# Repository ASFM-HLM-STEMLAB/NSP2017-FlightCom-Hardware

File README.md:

# NSP2017-FlightCom-Hardware 
ASFM Near Space Program 2017 - Flight Computer Hardware for HLM1 Capsule

- Designed in Autodesk Eagle.
- Uses Particle Electron as the master Micro Controller Unit

## Files
* HLM1_CNC : 
	This files are for creating a prototype board using a CNC such as shapeoko.
* HLM1_Oursourced : 
	This files are for sending the board to a fab house to be made such as OshPark

## PCB Manufacturing
* You may order a PCB from our [OSHPARK PROJECT R1.0](https://www.oshpark.com/projects/XPm0Xe82)
* You may order a PCB from our [OSHPARK PROJECT R2.1](https://www.adafruit.com/product/3686)
* NOTE: R2.1 includes XBee Radio. GPS IO changed to software serial.

##### Designed and created at ASFM Monterrey Mexico, 2017-2018 @ Humberto Lobo Morales STEM LAB

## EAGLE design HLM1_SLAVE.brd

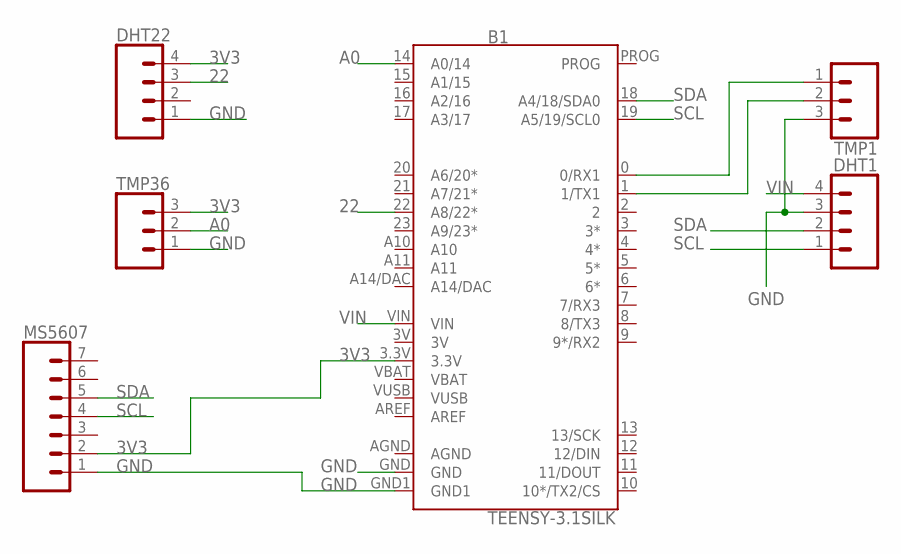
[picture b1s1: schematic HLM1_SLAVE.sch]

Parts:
B1: TEENSY-3.1SILK; TEENSY-3.1
DHT1, DHT22: CONN_04; 1X04
MS5607: CONN_07; 1X07
TMP1, TMP36: CONN_03; 1X03

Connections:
3V: B1.3V
3V3: B1.3.3V, DHT22.4, MS5607.2, TMP36.3
22: B1.22 (A8/22*), DHT22.3
A0: B1.14 (A0/14), TMP36.2
AGND: B1.AGND
GND: B1.GND, B1.GND1, DHT1.3, DHT22.1, MS5607.1, TMP1.3, TMP36.1
unnamed: B1.0 (0/RX1), TMP1.1
unnamed: B1.1 (1/TX1), TMP1.2
SCL: B1.19 (A5/19/SCL0), DHT1.1, MS5607.4
SDA: B1.18 (A4/18/SDA0), DHT1.2, MS5607.5
VBAT: B1.VBAT
VIN: B1.VIN, DHT1.4
VUSB: B1.VUSB

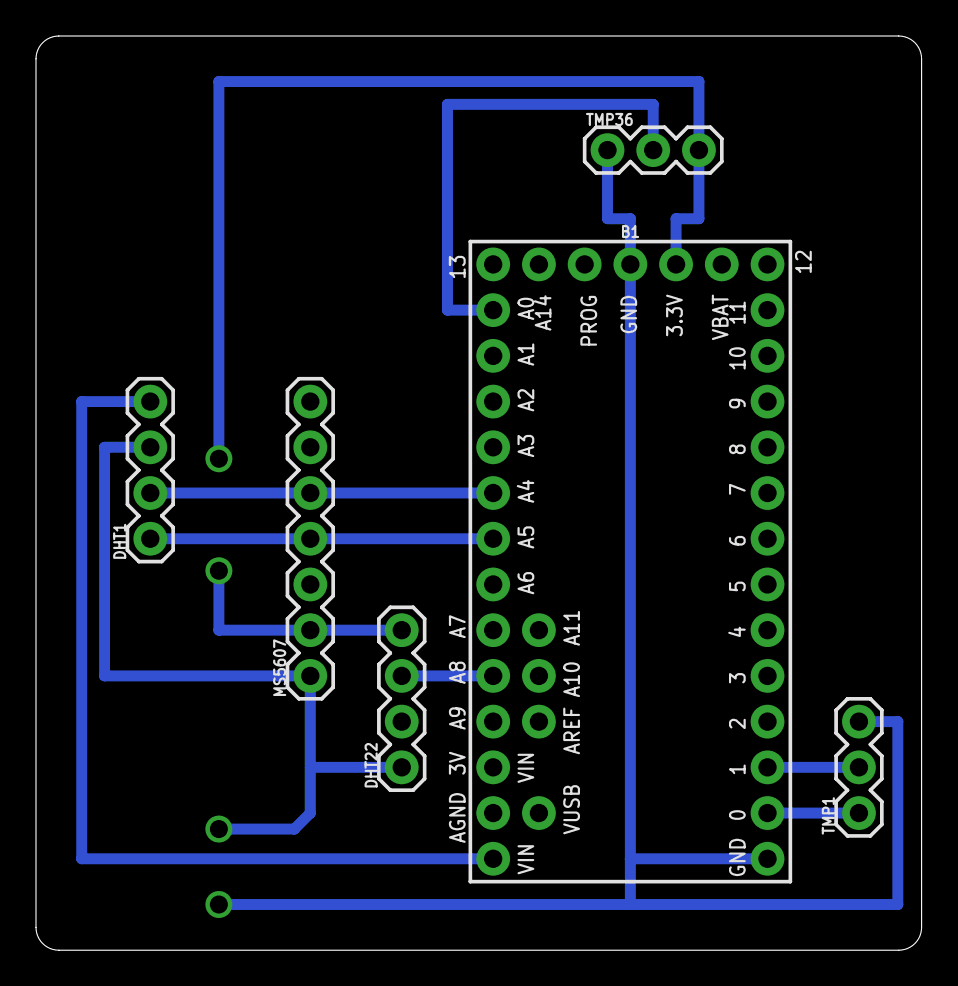
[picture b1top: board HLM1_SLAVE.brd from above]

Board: 2 copper layers, 49.2 x 50.8 mm, 6 parts (0 on the bottom side), 9 nets.

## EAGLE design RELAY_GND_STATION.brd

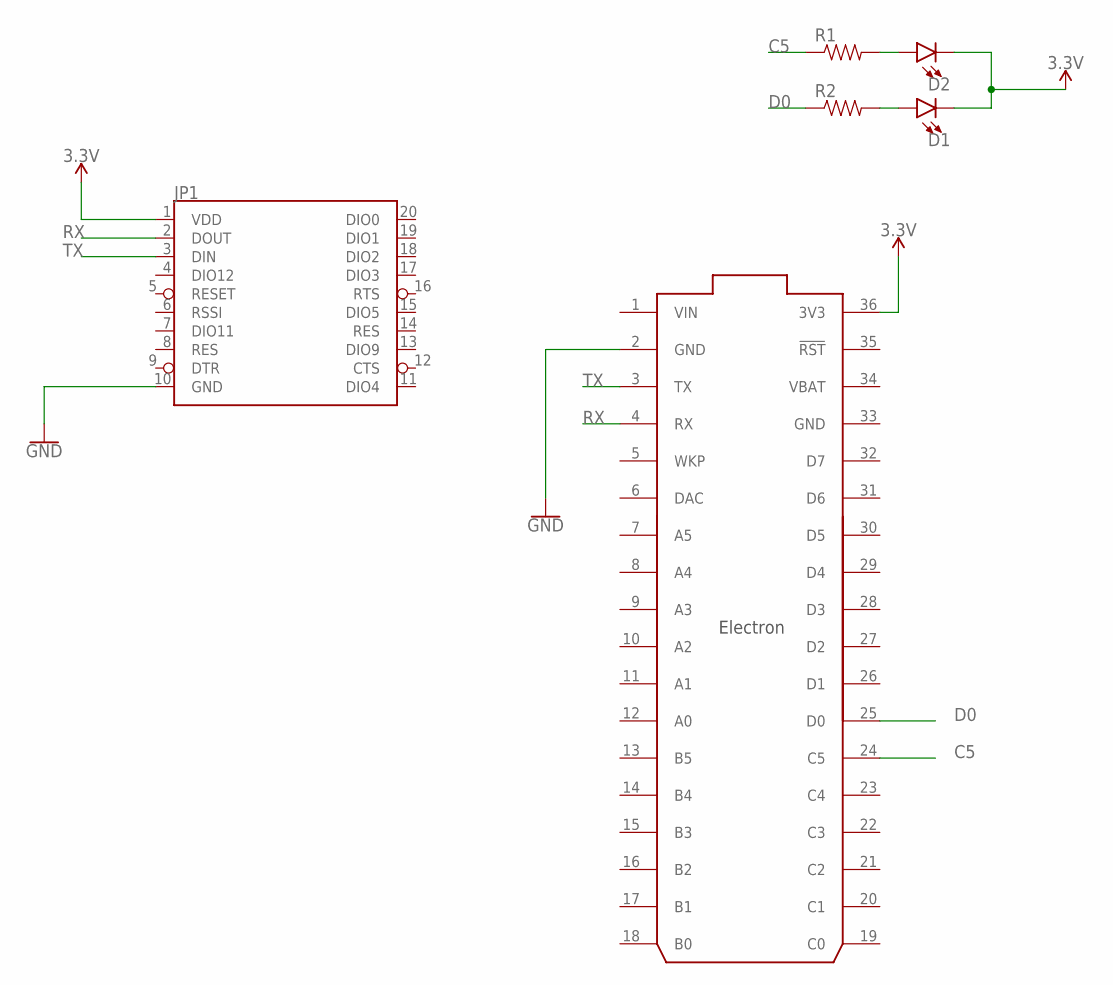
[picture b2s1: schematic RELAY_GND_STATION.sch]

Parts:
D1, D2: LED-3MM-NO_SILK; LED_3MM-NS
JP1: XBEELONGPAD; XBEE-LONGPAD
R1, R2: RESISTORKIT; AXIAL-0.3-KIT
U$1: ELECTRON_WITH_HEADERS; ELECTRON

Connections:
3.3V: D1.K (C), D2.K (C), JP1.1 (VDD), U$1.36 (3V3)
C5: R1.P$1 (1), U$1.24 (C5)
D0: R2.P$1 (1), U$1.25 (D0)
GND: JP1.10 (GND), U$1.2 (GND), U$1.33 (GND)
unnamed: D2.A, R1.P$2 (2)
unnamed: D1.A, R2.P$2 (2)
RX: JP1.2 (DOUT), U$1.4 (RX)
TX: JP1.3 (DIN), U$1.3 (TX)
VBAT: U$1.34 (VBAT)
VIN: U$1.1 (VIN)

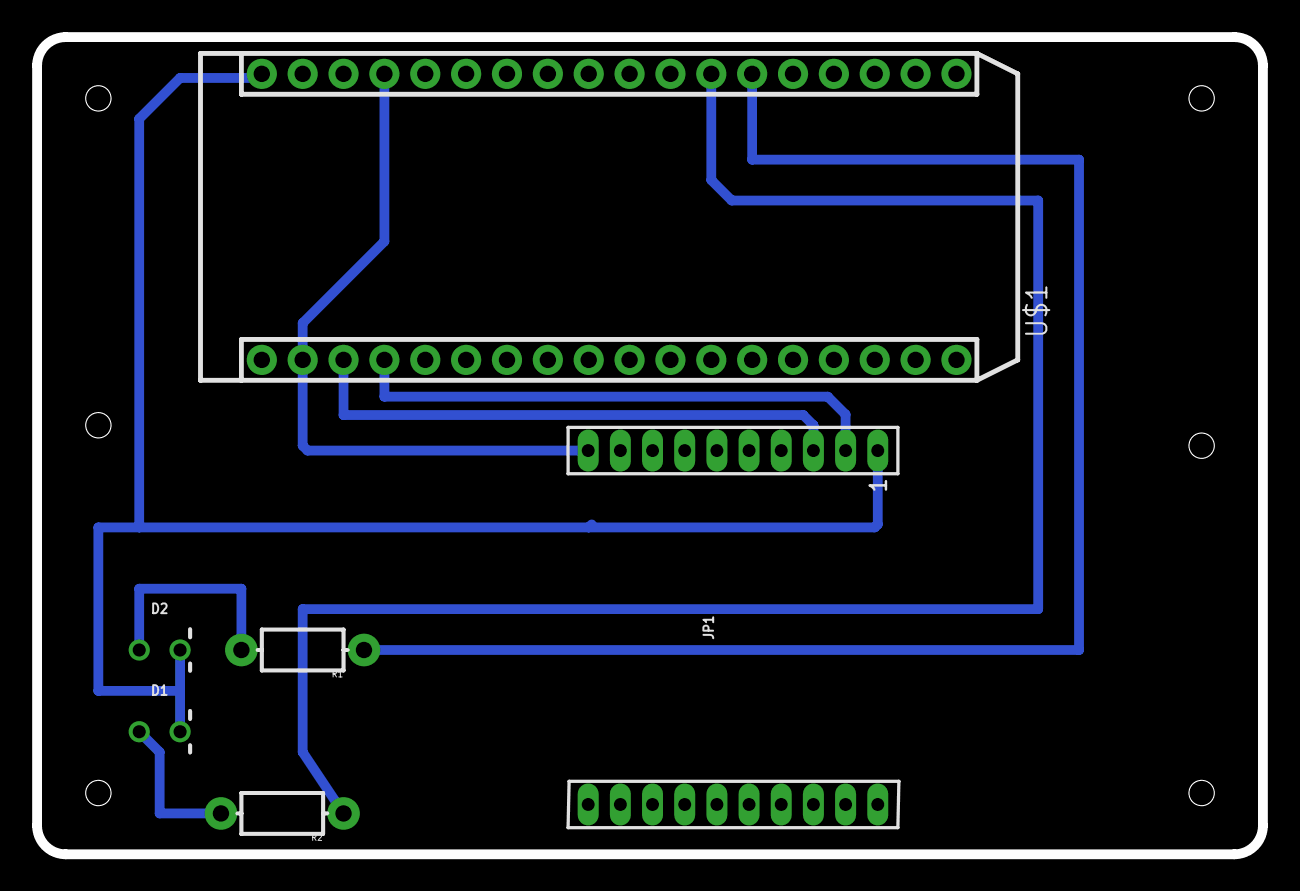
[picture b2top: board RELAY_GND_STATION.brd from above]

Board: 2 copper layers, 76.2 x 50.8 mm, 6 parts (0 on the bottom side), 8 nets.

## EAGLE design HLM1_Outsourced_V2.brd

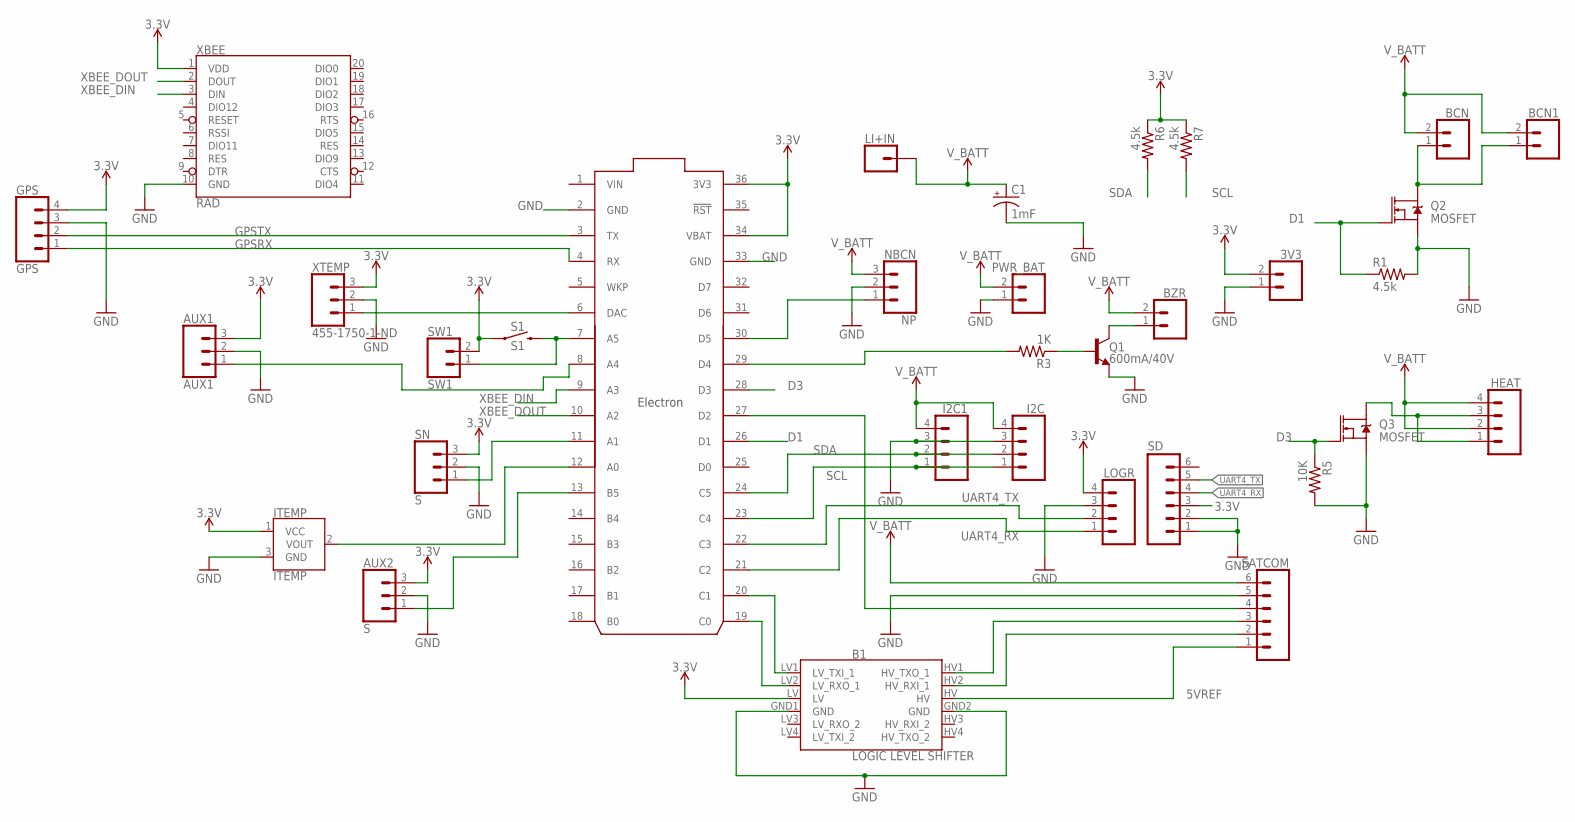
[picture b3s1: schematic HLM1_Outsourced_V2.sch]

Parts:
3V3: CONN_02; 1X02
AUX1: AUX1; 1X03
AUX2: S; 1X03
B1: LOGIC LEVEL SHIFTER; SPARKFUN_LOGIC_LEVEL_CONVERTER
BCN, BCN1: CONN_02; 1X02
BZR: CONN_02; 1X02
C1: 1mF; CPOL-RADIAL-5MM-10MM
GPS: GPS; 1X04
HEAT: CONN_04; 1X04
I2C, I2C1: CONN_04; 1X04
ITEMP: ITEMP; TO-92
LI+IN: CONN_01; 1X01
LOGR: CONN_04; 1X04
MCU: ELECTRON
NBCN: NP; 1X03
PWR_BAT: CONN_02; 1X02
Q1: 600mA/40V; TO-92
Q2, Q3: MOSFET; TO220V
R1, R6, R7: 4.5k; 1/6W-RES
R3: 1K; 1/6W-RES
R5: 10K; 1/6W-RES
S1: S1; TACTILE_SWITCH_PTH_6.0MM
SATCOM: CONN_06SILK_FEMALE_PTH; 1X06@1
SD: M06NO_SILK_FEMALE_PTH; 1X06_NO_SILK
SN: S; 1X03
SW1: SW1; 1X02
XBEE: RAD; XBEE-LONGPAD
XTEMP: 455-1750-1-ND; 1X03

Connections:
3.3V: 3V3.2, AUX1.3, AUX2.3, B1.LV, GPS.4, ITEMP.1 (VCC), LOGR.4, MCU.34 (VBAT), MCU.36 (3V3), R6.1, R7.1, S1.1, SD.3, SN.3, SW1.2, XBEE.1 (VDD), XTEMP.3
5VREF: B1.HV, SATCOM.1
D1: MCU.26 (D1), Q2.1 (G), R1.1
D3: MCU.28 (D3), Q3.1 (G), R5.1
GND: 3V3.1, AUX1.2, AUX2.2, B1.GND1 (GND), B1.GND2 (GND), C1.-, GPS.3, I2C.3, I2C1.3, ITEMP.3 (GND), LOGR.3, MCU.2 (GND), MCU.33 (GND), NBCN.2, PWR_BAT.1, Q1.3 (E), Q2.3 (S), Q3.3 (S), R1.2, R5.2, SATCOM.5, SD.1, SD.2, SN.2, XBEE.10 (GND), XTEMP.2
GPSRX: GPS.1, MCU.4 (RX)
GPSTX: GPS.2, MCU.3 (TX)
IRWKP: MCU.27 (D2), SATCOM.4
unnamed: MCU.6 (DAC), XTEMP.1
unnamed: MCU.29 (D4), R3.2
unnamed: Q1.2 (B), R3.1
unnamed: MCU.30 (D5), NBCN.1
unnamed: B1.LV1 (LV_TXI_1), MCU.20 (C1)
unnamed: B1.LV2 (LV_RXO_1), MCU.19 (C0)
unnamed: BZR.1, Q1.1 (C)
unnamed: B1.HV1 (HV_TXO_1), SATCOM.3
unnamed: HEAT.1, HEAT.3, Q3.2 (D)
unnamed: BCN.1, BCN1.1, Q2.2 (D)
unnamed: B1.HV2 (HV_RXI_1), SATCOM.2
unnamed: MCU.7 (A5), S1.3 (2), SW1.1
unnamed: MCU.11 (A1), SN.1
unnamed: ITEMP.2 (VOUT), MCU.12 (A0)
unnamed: AUX2.1, MCU.13 (B5)
unnamed: AUX1.1, MCU.8 (A4)
SCL: I2C.1, I2C1.1, MCU.23 (C4), R7.2
SDA: I2C.2, I2C1.2, MCU.24 (C5), R6.2
UART4_RX: LOGR.1, MCU.21 (C2), SD.4
UART4_TX: LOGR.2, MCU.22 (C3), SD.5
VIN: MCU.1 (VIN)
V_BATT: BCN.2, BCN1.2, BZR.2, C1.+, HEAT.2, HEAT.4, I2C.4, I2C1.4, LI+IN.1, NBCN.3, PWR_BAT.2, SATCOM.6
XBEE_DIN: MCU.9 (A3), XBEE.3 (DIN)
XBEE_DOUT: MCU.10 (A2), XBEE.2 (DOUT)

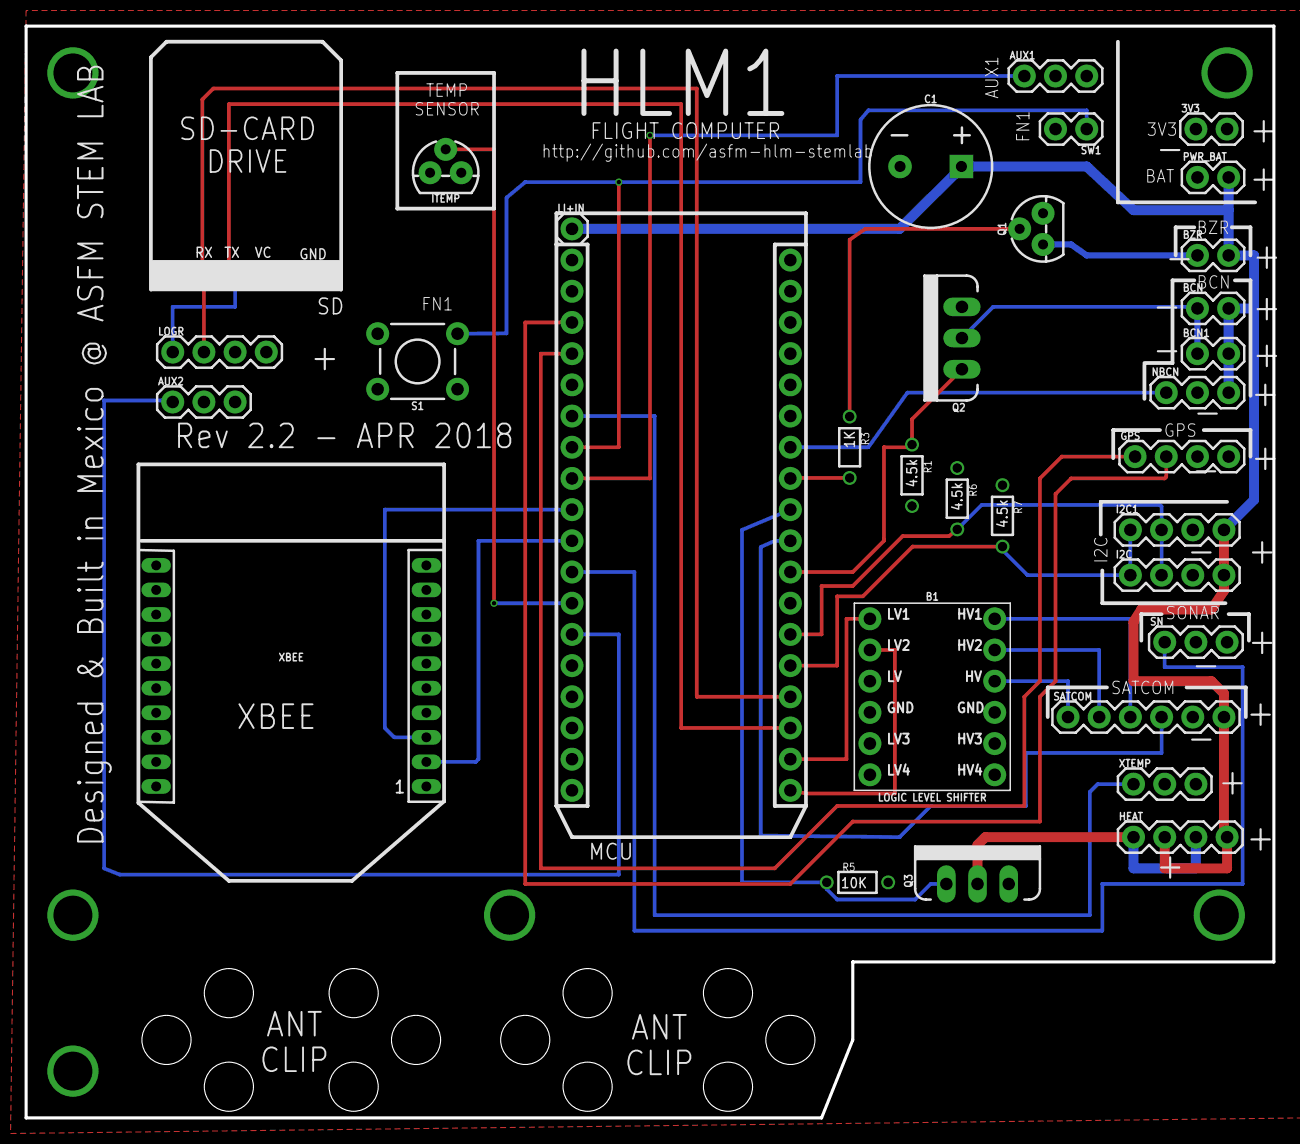
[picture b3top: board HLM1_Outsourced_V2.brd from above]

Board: 2 copper layers, 101.6 x 88.9 mm, 33 parts (0 on the bottom side), 31 nets.

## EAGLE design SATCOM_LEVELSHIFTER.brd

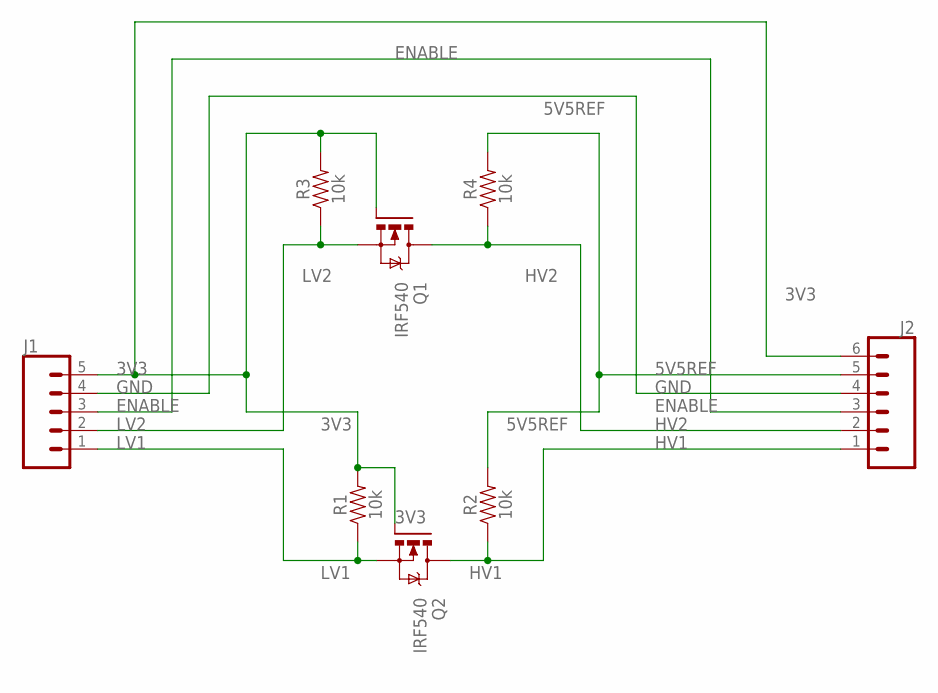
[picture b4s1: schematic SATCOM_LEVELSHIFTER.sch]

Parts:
J1: CONN_05PTH_LONGPADS; 1X05_LONGPADS
J2: CONN_06LONGPADS; 1X06_LONGPADS
Q1, Q2: IRF540; TO220BV
R1, R2, R3, R4: 10k; AXIAL-0.3-KIT

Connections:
3V3: J1.5, J2.6, Q1.G, Q2.G, R1.P$2 (2), R3.P$2 (2)
5V5REF: J2.5, R2.P$2 (2), R4.P$2 (2)
ENABLE: J1.3, J2.3
GND: J1.4, J2.4
HV1: J2.1, Q2.D, R2.P$1 (1)
HV2: J2.2, Q1.D, R4.P$1 (1)
LV1: J1.1, Q2.S, R1.P$1 (1)
LV2: J1.2, Q1.S, R3.P$1 (1)

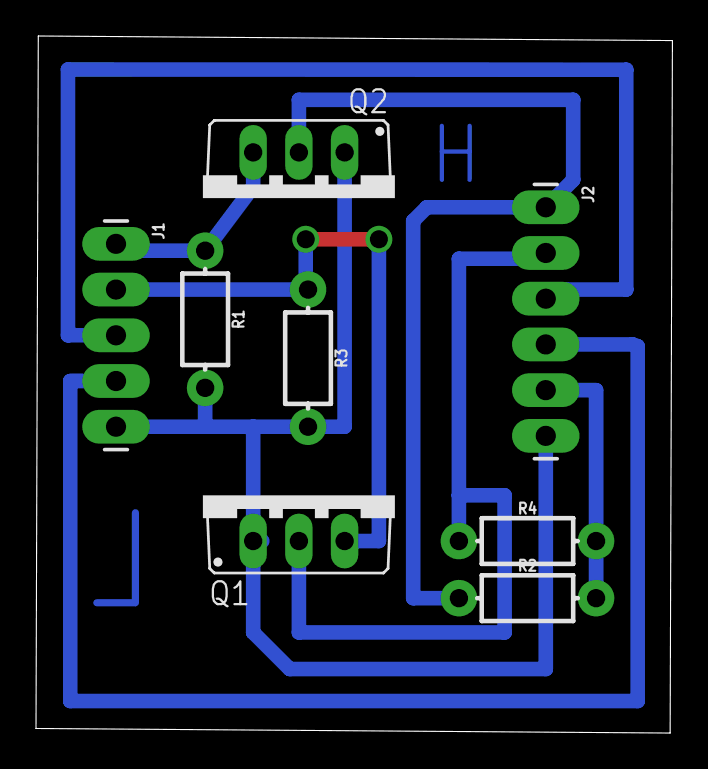
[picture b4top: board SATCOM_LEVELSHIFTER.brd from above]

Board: 2 copper layers, 35.4 x 38.7 mm, 8 parts (0 on the bottom side), 8 nets.

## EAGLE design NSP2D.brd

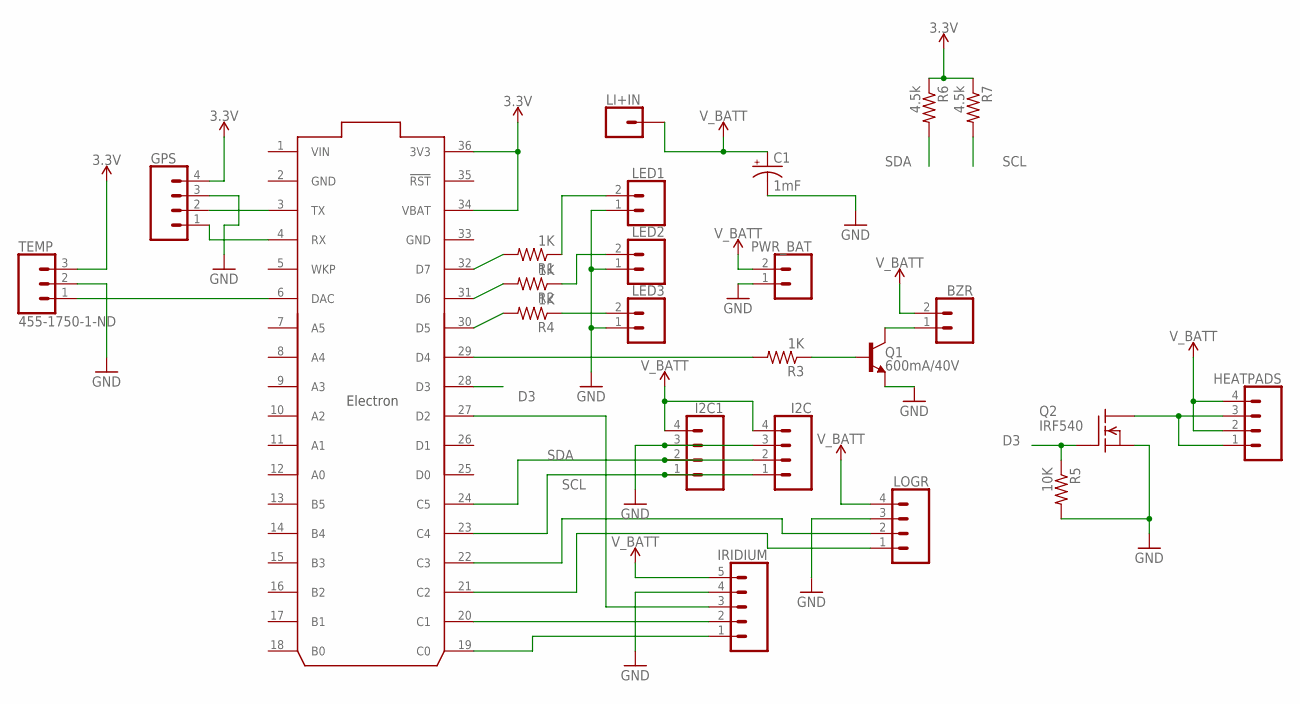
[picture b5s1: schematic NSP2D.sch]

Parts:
BZR: CONN_02; 1X02
C1: 1mF; CPOL-RADIAL-5MM-10MM
GPS: CONN_04; 1X04
HEATPADS: CONN_04; 1X04
I2C, I2C1: CONN_04; 1X04
IRIDIUM: CONN_05; 1X05
LED1, LED2, LED3: CONN_02; 1X02
LI+IN: CONN_01; 1X01
LOGR: CONN_04; 1X04
MCU: ELECTRON
PWR_BAT: CONN_02; 1X02
Q1: 600mA/40V; TO-92
Q2: IRF540; TO220
R1, R2, R3, R4: 1K; 1/6W-RES
R5: 10K; 1/6W-RES
R6, R7: 4.5k; 1/6W-RES
TEMP: 455-1750-1-ND; 1X03

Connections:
3.3V: GPS.4, MCU.34 (VBAT), MCU.36 (3V3), R6.1, R7.1, TEMP.3
D3: MCU.28 (D3), Q2.1 (G), R5.1
GND: C1.-, GPS.3, I2C.3, I2C1.3, IRIDIUM.4, LED1.1, LED2.1, LED3.1, LOGR.3, MCU.2 (GND), MCU.33 (GND), PWR_BAT.1, Q1.3 (E), Q2.3 (S), R5.2, TEMP.2
IRWKP: IRIDIUM.3, MCU.27 (D2)
unnamed: MCU.6 (DAC), TEMP.1
unnamed: GPS.2, MCU.3 (TX)
unnamed: MCU.32 (D7), R1.2
unnamed: Q1.2 (B), R3.1
unnamed: MCU.29 (D4), R3.2
unnamed: LED1.2, R1.1
unnamed: BZR.1, Q1.1 (C)
unnamed: HEATPADS.1, HEATPADS.3, Q2.2 (D)
unnamed: GPS.1, MCU.4 (RX)
unnamed: MCU.31 (D6), R2.2
unnamed: IRIDIUM.2, MCU.20 (C1)
unnamed: LED2.2, R2.1
unnamed: MCU.30 (D5), R4.2
unnamed: LED3.2, R4.1
SCL: I2C.1, I2C1.1, MCU.23 (C4), R7.2
SDA: I2C.2, I2C1.2, MCU.24 (C5), R6.2
UART4_RX: LOGR.1, MCU.21 (C2)
UART4_TX: LOGR.2, MCU.22 (C3)
UART5_RX: IRIDIUM.1, MCU.19 (C0)
VIN: MCU.1 (VIN)
V_BATT: BZR.2, C1.+, HEATPADS.2, HEATPADS.4, I2C.4, I2C1.4, IRIDIUM.5, LI+IN.1, LOGR.4, PWR_BAT.2

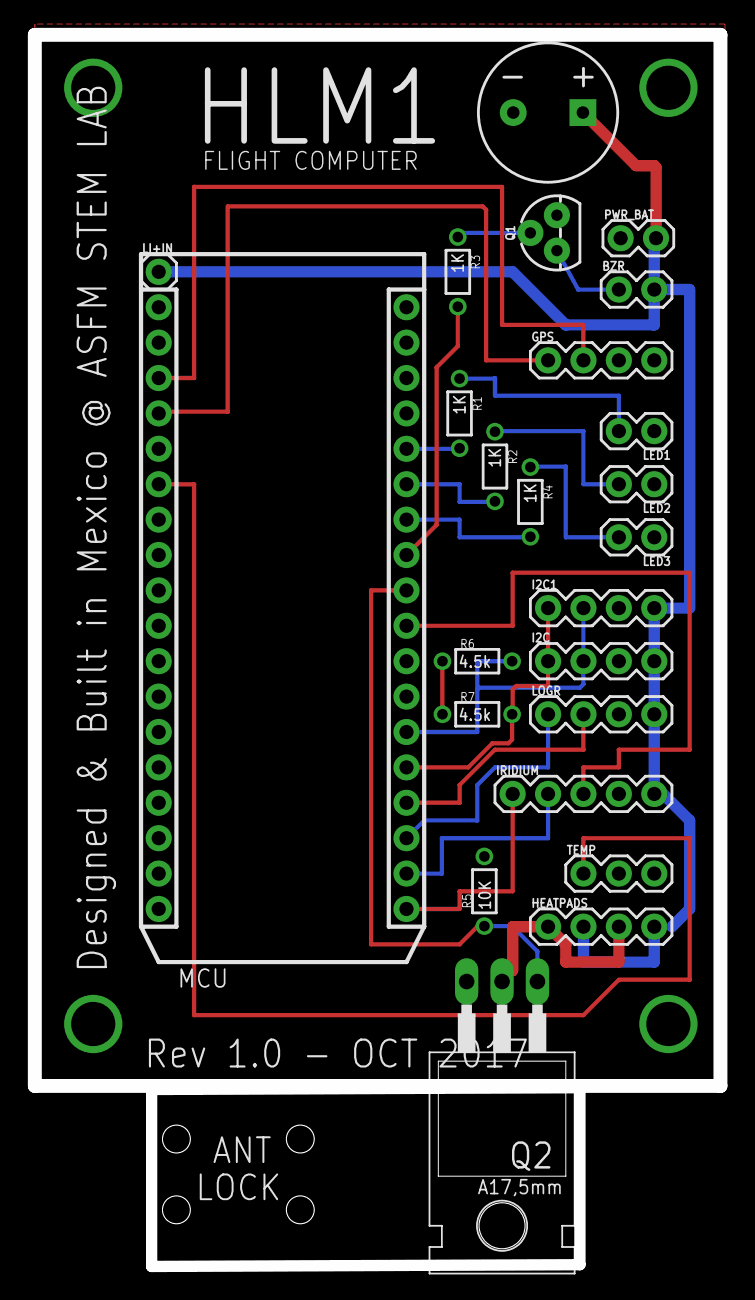
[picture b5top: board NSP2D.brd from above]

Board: 2 copper layers, 49.2 x 88.3 mm, 24 parts (0 on the bottom side), 24 nets.

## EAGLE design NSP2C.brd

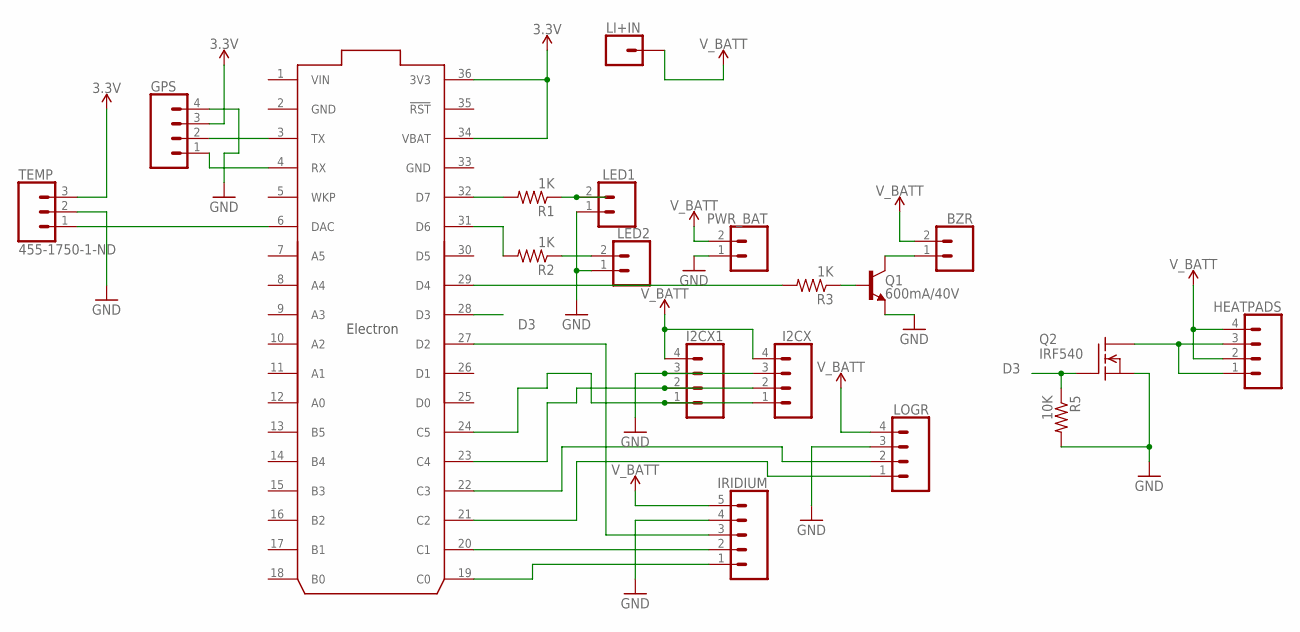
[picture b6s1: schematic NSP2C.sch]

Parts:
BZR: CONN_02; 1X02
GPS: CONN_04; 1X04
HEATPADS: CONN_04; 1X04
I2CX, I2CX1: CONN_04; 1X04
IRIDIUM: CONN_05; 1X05
LED1, LED2: CONN_02; 1X02
LI+IN: CONN_01; 1X01
LOGR: CONN_04; 1X04
PWR_BAT: CONN_02; 1X02
Q1: 600mA/40V; TO-92
Q2: IRF540; TO220
R1, R2, R3: 1K; 1/6W-RES
R5: 10K; 1/6W-RES
TEMP: 455-1750-1-ND; 1X03
U$1: ELECTRON_WITH_HEADERS; ELECTRON

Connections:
3.3V: GPS.3, TEMP.3, U$1.34 (VBAT), U$1.36 (3V3)
BASE: Q1.2 (B), R3.1
D3: Q2.1 (G), R5.1, U$1.28 (D3)
GND: GPS.4, I2CX.3, I2CX1.3, IRIDIUM.4, LED1.1, LED2.1, LOGR.3, PWR_BAT.1, Q1.3 (E), Q2.3 (S), R5.2, TEMP.2, U$1.2 (GND), U$1.33 (GND)
IRWKP: IRIDIUM.3, U$1.27 (D2)
unnamed: TEMP.1, U$1.6 (DAC)
unnamed: R1.2, U$1.32 (D7)
unnamed: R3.2, U$1.29 (D4)
unnamed: LED1.2, R1.1
unnamed: BZR.1, Q1.1 (C)
unnamed: HEATPADS.1, HEATPADS.3, Q2.2 (D)
unnamed: R2.2, U$1.31 (D6)
unnamed: IRIDIUM.2, U$1.20 (C1)
unnamed: I2CX.1, I2CX1.1, U$1.24 (C5)
unnamed: LED2.2, R2.1
RX: GPS.1, U$1.4 (RX)
SDA: I2CX.2, I2CX1.2, U$1.23 (C4)
TX: GPS.2, U$1.3 (TX)
UART4_RX: LOGR.1, U$1.21 (C2)
UART4_TX: LOGR.2, U$1.22 (C3)
UART5_RX: IRIDIUM.1, U$1.19 (C0)
VIN: U$1.1 (VIN)
V_BATT: BZR.2, HEATPADS.2, HEATPADS.4, I2CX.4, I2CX1.4, IRIDIUM.5, LI+IN.1, LOGR.4, PWR_BAT.2

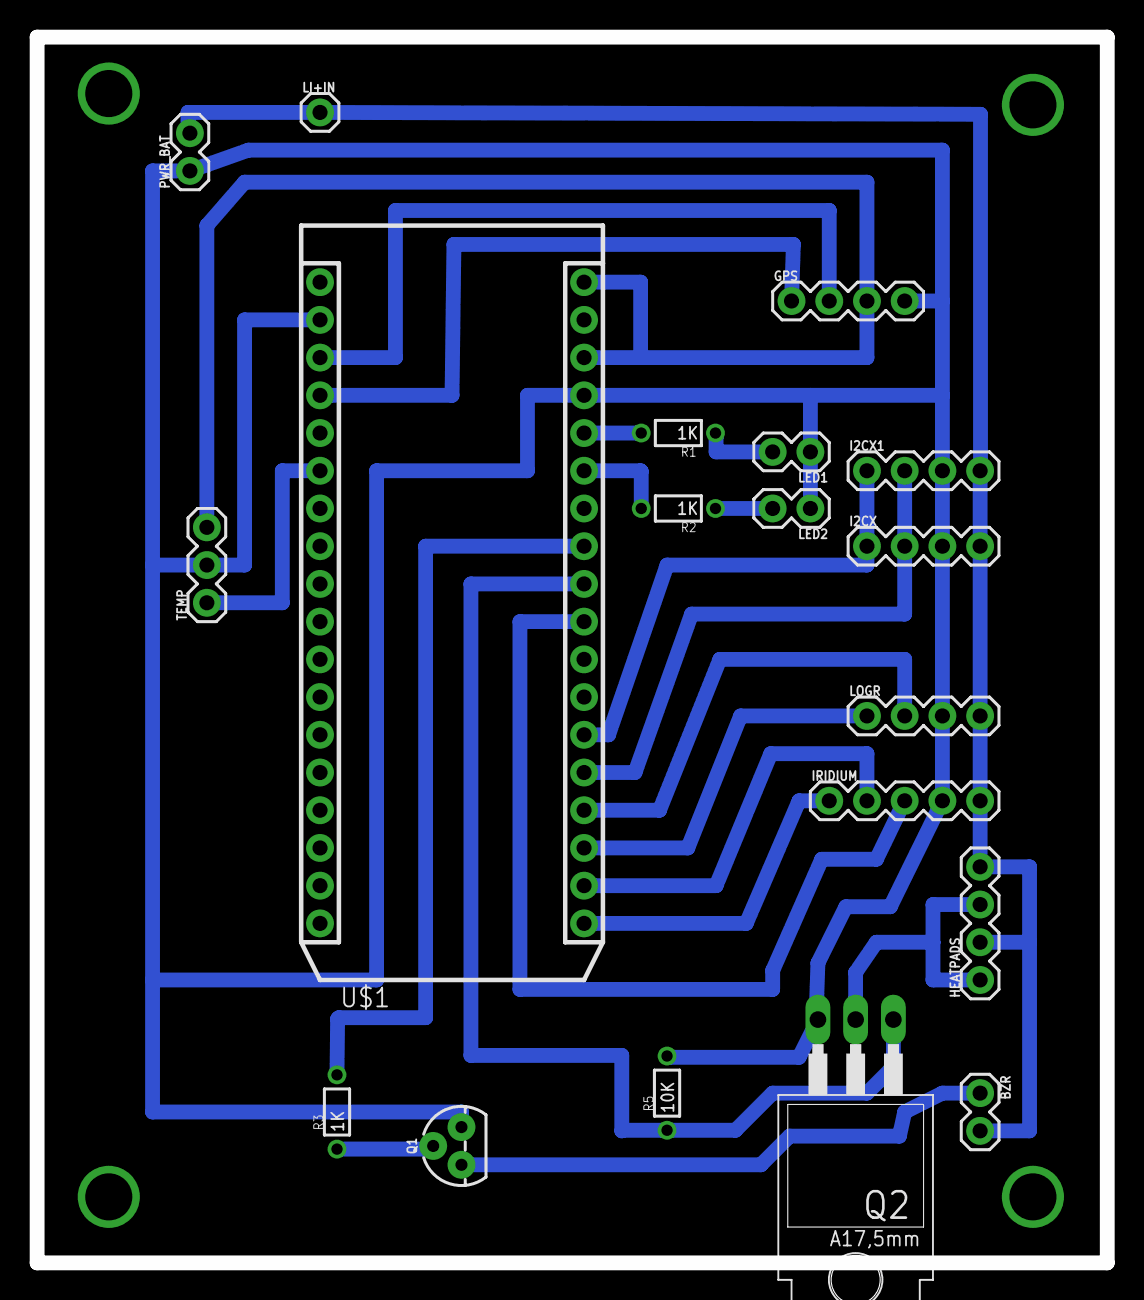
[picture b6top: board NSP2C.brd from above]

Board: 2 copper layers, 72.1 x 82.5 mm, 19 parts (0 on the bottom side), 22 nets.

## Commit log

2017-10-24 Added routes to PCB in 1 Lauyer (VC)
2017-10-24 Made width of wires thicker (1.00mm)
2017-10-24 Improved routing
2017-10-26 Added new PCB design for outsource manufacturing
2017-10-26 Added missing pullup resistors to SCL SDA for I2C bus
2017-10-31 Added capacitor for batt source
2017-10-31 Finished R1 for manufacturing
2017-11-03 Improved naming and file structure
2017-11-03 Improved ignore for git
2017-11-03 .DS_Store banished!
2017-11-03 Tried to remove DS again
2017-11-03 Improved naming conventions for GIT
2017-11-05 Added onboard level shifter to outsourced design and other improvements
2017-11-05 Added onboard SD CARD + Sonar Port for touchdown detection
2017-11-05 Improved design and labels
2017-11-27 Incremental
2017-11-27 Added PCB V1.1 PDF for reference
2018-02-02 Minor Updates
2018-04-06 Implemented version 2.1 for XBee Radio + Improvements throughout
2018-04-06 Added oshpark link of R2.1 to Readme file of repository
2018-04-06 Minor tweaks to Readme file
2018-04-28 Updated flight board to add XBee radio
2018-05-07 Slave board added
2018-05-13 Connected I2C lines to slave device for board carving

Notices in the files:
parts and their libraries:
SparkFun-Connectors: Licensing: Creative Commons ShareAlike 4.0 International - https://creativecommons.org/licenses/by-sa/4.0
Particle-Devices: Licensing: Designed by Particle.
